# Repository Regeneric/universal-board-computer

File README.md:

# EXPERIMENTAL

Experimental branch for Pico W, written in Golang with TinyGO
Nothing works, really.

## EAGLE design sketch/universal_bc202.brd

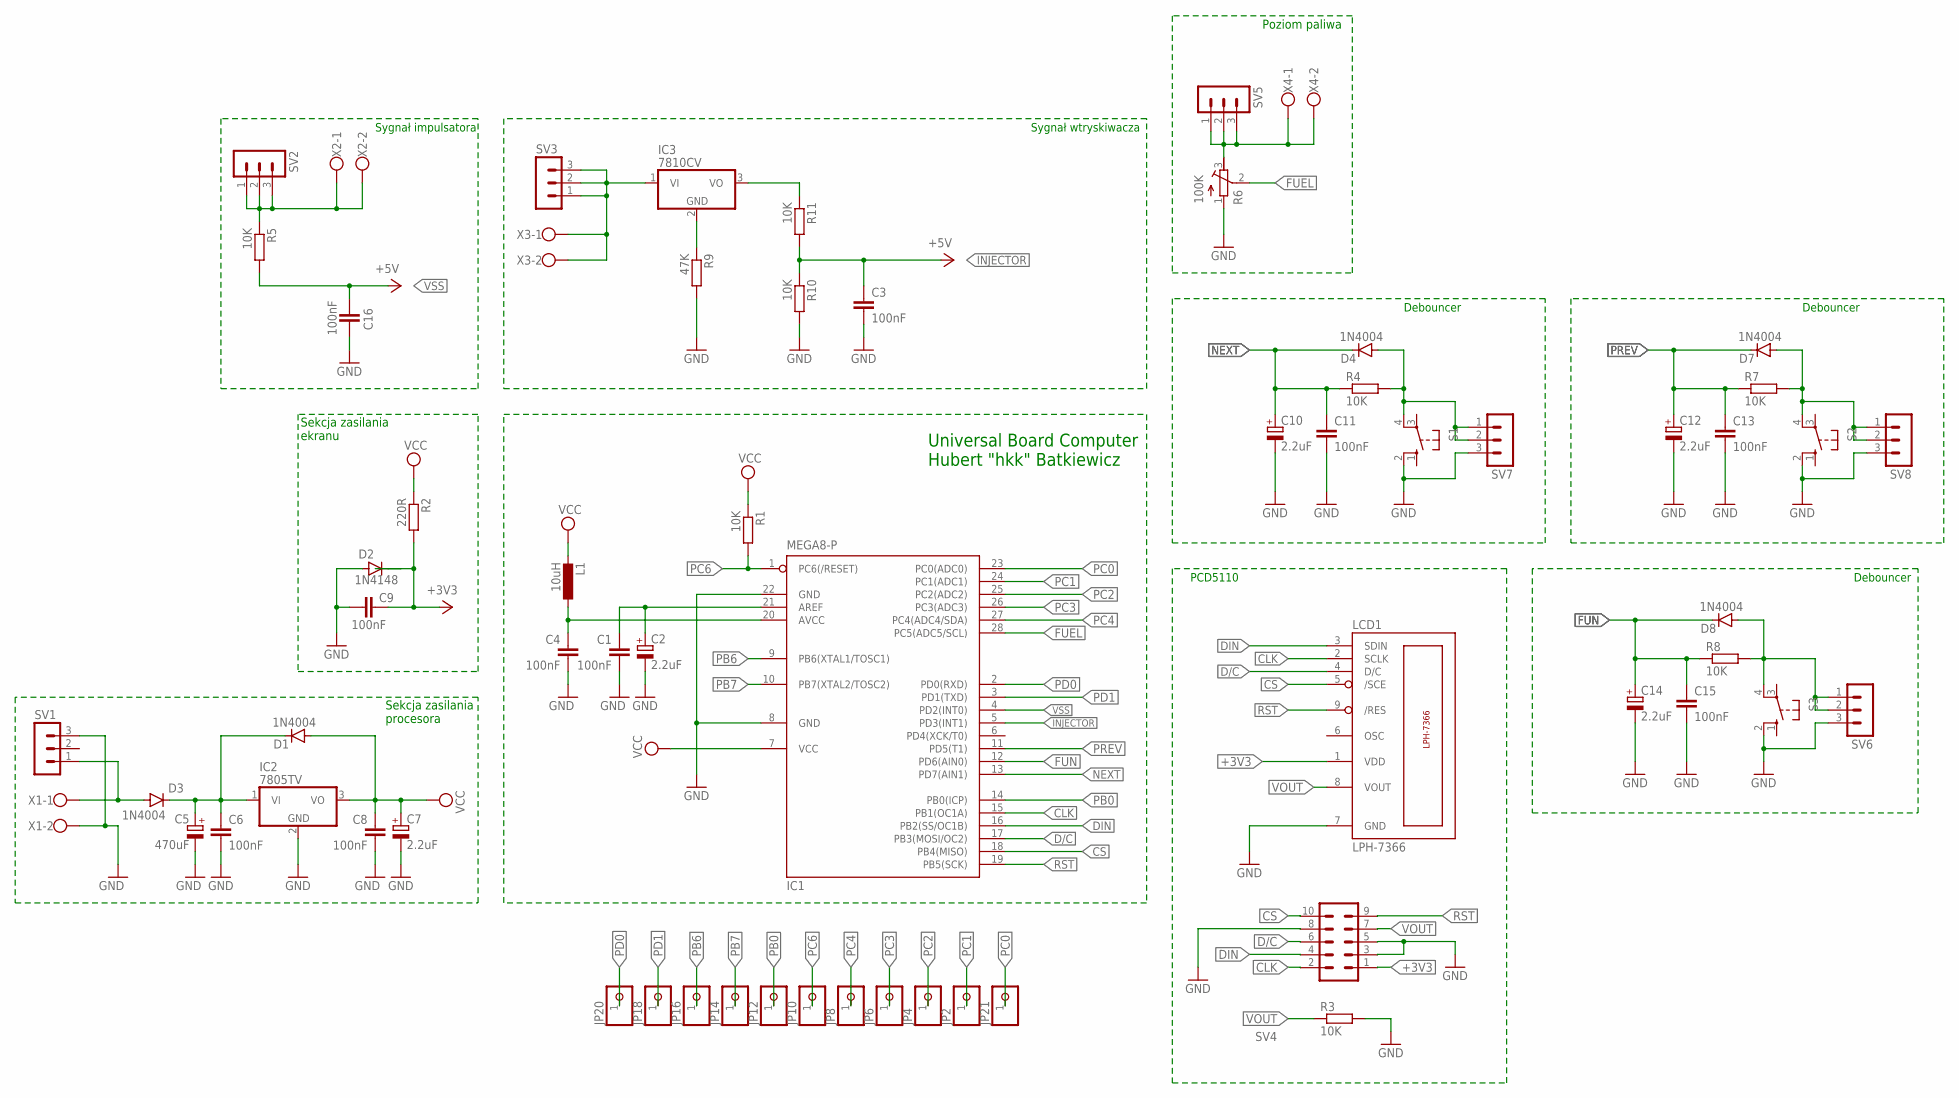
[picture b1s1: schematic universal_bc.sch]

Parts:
C1, C3, C4, C6, C8, C9, C11, C13, C15, C16: 100nF; C025-025X050
C2, C7, C10, C12, C14: 2.2uF; E2,5-6E
C5: 470uF; E2,5-6E
D1, D3, D4, D7, D8: 1N4004; DO41-10
D2: 1N4148; DO35-7
IC1: MEGA8-P; DIL28-3
IC2: 7805TV; TO220V
IC3: 7810CV; TO220V
JP2, JP4, JP6, JP8, JP10, JP12, JP14, JP16, JP18, JP20, JP21: PINHD-1X1; 1X01
L1: 10uH; 0207/2V
LCD1: LPH-7366
R1, R3, R4, R5, R7, R8, R10, R11: 10K; 0207/10
R2: 220R; 0207/10
R6: 100K; RTRIM3339P
R9: 47K; 0207/10
S1, S2, S3: 10-XX; B3F-10XX
SV1, SV2, SV3, SV5, SV6, SV7, SV8: MA03-1
SV4: MA05-2
X1, X2, X3, X4: W237-102

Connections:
+3V3: C9.1, D2.C, LCD1.1 (VDD), R2.2, SV4.1
CLK: IC1.15 (PB1(OC1A)), LCD1.2 (SCLK), SV4.2
CS: IC1.18 (PB4(MISO)), LCD1.5 (/SCE), SV4.10
D/C: IC1.17 (PB3(MOSI/OC2)), LCD1.4 (D/C), SV4.6
DIN: IC1.16 (PB2(SS/OC1B)), LCD1.3 (SDIN), SV4.4
FLOAT: R6.3 (E), SV5.1, SV5.2, SV5.3, X4.1, X4.2
FUEL: IC1.28 (PC5(ADC5/SCL)), R6.2 (S)
FUN: C14.+, C15.1, D8.C, IC1.12 (PD6(AIN0)), R8.1
GND: C1.2, C2.-, C3.2, C4.2, C5.-, C6.2, C7.-, C8.2, C9.2, C10.-, C11.2, C12.-, C13.2, C14.-, C15.2, C16.1, D2.A, IC1.8 (GND), IC1.22 (GND), IC2.2 (GND), LCD1.7 (GND), R3.2, R6.1 (A), R9.2, R10.2, S1.2 (S1), S2.2 (S1), S3.2 (S1), SV1.3, SV4.3, SV4.5, SV4.8, SV6.3, SV7.3, SV8.3, X1.2; also elsewhere on the board
INJECTOR: C3.1, IC1.5 (PD3(INT1)), R10.1, R11.2
unnamed: C1.1, C2.+, IC1.21 (AREF)
unnamed: C4.1, IC1.20 (AVCC), L1.1
unnamed: C5.+, C6.1, D1.C, D3.C, IC2.1 (VI)
unnamed: IC3.1 (VI), SV3.1, SV3.2, SV3.3, X3.1, X3.2
unnamed: D4.A, R4.2, S1.4 (P1), SV7.1, SV7.2
unnamed: D7.A, R7.2, S2.4 (P1), SV8.1, SV8.2
unnamed: D8.A, R8.2, S3.4 (P1), SV6.1, SV6.2
unnamed: D3.A, SV1.1, X1.1
unnamed: R5.1, SV2.1, SV2.2, SV2.3, X2.1, X2.2
unnamed: IC3.2 (GND), R9.1
unnamed: IC3.3 (VO), R11.1
NEXT: C10.+, C11.1, D4.C, IC1.13 (PD7(AIN1)), R4.1
PB0: IC1.14 (PB0(ICP)), JP12.1
PB6: IC1.9 (PB6(XTAL1/TOSC1)), JP16.1
PB7: IC1.10 (PB7(XTAL2/TOSC2)), JP14.1
PC0: IC1.23 (PC0(ADC0)), JP21.1
PC1: IC1.24 (PC1(ADC1)), JP2.1
PC2: IC1.25 (PC2(ADC2)), JP4.1
PC3: IC1.26 (PC3(ADC3)), JP6.1
PC4: IC1.27 (PC4(ADC4/SDA)), JP8.1
PC6: IC1.1 (PC6(/RESET)), JP10.1, R1.2; also elsewhere on the board
PD0: IC1.2 (PD0(RXD)), JP20.1
PD1: IC1.3 (PD1(TXD)), JP18.1
PREV: C12.+, C13.1, D7.C, IC1.11 (PD5(T1)), R7.1
RST: IC1.19 (PB5(SCK)), LCD1.9 (/RES), SV4.9
VCC: C7.+, C8.1, D1.A, IC1.7 (VCC), IC2.3 (VO), L1.2, R1.1, R2.1; also elsewhere on the board
VOUT: LCD1.8 (VOUT), R3.1, SV4.7
VSS: C16.2, IC1.4 (PD2(INT0)), R5.2

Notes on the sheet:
Sekcja zasilania procesora
Sekcja zasilania ekranu
Universal Board Computer Hubert "hkk" Batkiewicz
PCD5110
Sygnał impulsatora
Debouncer
Sygnał wtryskiwacza
Poziom paliwa

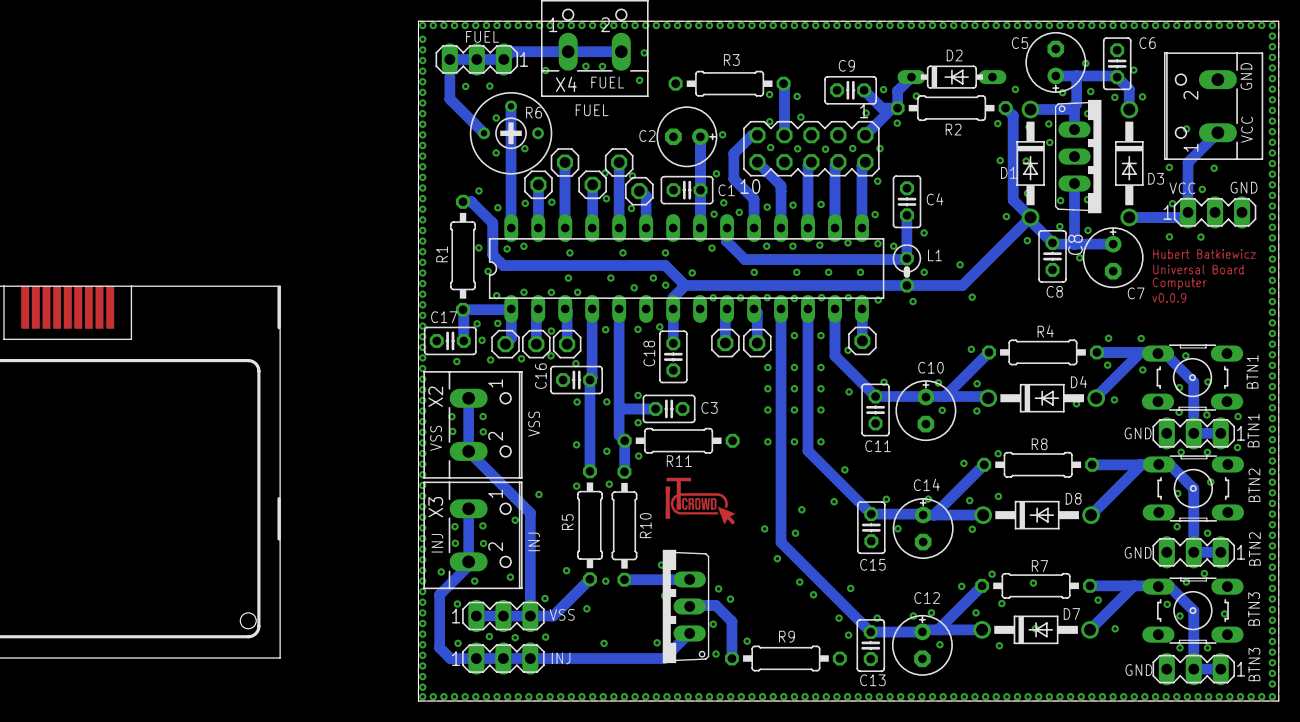
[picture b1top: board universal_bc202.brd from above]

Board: 2 copper layers, 81.0 x 64.0 mm, 66 parts (0 on the bottom side), 38 nets.

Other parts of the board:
C17: 10nF; C025-025X050
C18: 100nF; C025-025X050

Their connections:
GND: C17.2, C18.2; also elsewhere on the board
PC6: C17.1; also elsewhere on the board
VCC: C18.1; also elsewhere on the board

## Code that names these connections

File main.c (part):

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
    #define DHT_DDR  DDRD          
    #define DHT_PORT PORTD
    #define DHT_PIN  (1<<5)                    // PD5 as DHT11 pin

    #define DHT_EN_OUT  DHT_DDR |= DHT_PIN     // PD5 as output
    #define DHT_EN_INP  DHT_DDR &= ~DHT_PIN    // PD5 as input

    #define DHT_LO   DHT_PORT &= ~DHT_PIN      // Low state on PD5
    #define DHT_HI   DHT_PORT |= DHT_PIN       // High state on PD5

    typedef struct {
        float humidity;
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    } DHT; DHT dht;
#endif

#define USE_ADC              1        // 0 - don't use ADC for fuel readings;  1 - use ADC for fuel readings
#define INJECTORS            4        // Number of injectors

#define SAVE_INTERVAL        60       // Save data to EEPROM every X seconds
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
    #if USE_ADC == 1
    // ADC for checking fuel level
    DDRC &= ~(1<<PC5);                                // PC5/ADC as input

    ADCSRA |= ((1<<ADEN) | (1<<ADPS2) | (1<<ADPS1));  // Enables ADC and sets prescaller to 64 (8 MHz, 128 for 16 MHz)
    ADMUX |= ((1<<REFS1) | (1<<REFS0));               // Internal 1.1V ref voltage with external capacitor
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

    // VSS signal and injector signal - Atmega 328
    DDRD &= ~((1<<PD3) | (1<<PD2));      // PD3/INT1 and PD2/INT0 as input
    PORTD |= ((1<<PD3) | (1<<PD2));      // PD2/INT0 and PD3/INT1internal pull-up resistor to avoid high impedance state of the pin

    EICRA |= (1<<ISC01);                 // The FALLING edge on INT0 generates interrupt
    EICRA |= (1<<ISC10);                 // ANY change of state of INT1 generates interrupt
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    

    // Navigation buttons - Atmega 328
    DDRD &= ~((1<<PD7) | (1<<PD6));      // PD7/PCINT23 and PD6 as input    
    PORTD |= ((1<<PD7) | (1<<PD6));      // PD7/PCINT23 and PD6 internal pull-up resistor

    DDRB &= ~(1<<PB0);                   // PB0/PCINT0 as input
    PORTB |= (1<<PB0);                   // PB0/PCINT0 internal pull-up resistor

    PCICR |= ((1<<PCIE0) | (1<<PCIE2));  // Set PCIE0 and PCIE2 to enable PCMSK0 and PCMSK2 scan
    PCIFR |= ((1<<PCIF0) | (1<<PCIF2));  // Set PCIF0 and PCIF2 to enable interrupt flasg mask
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            fuelLeft = 40;
        #endif
        
        if(!(PIND & (1<<PD6)) && !buttonPressed) {
            while(i != 0) --i;
            i = 15;

            PORTD = i | (1<<PD6);
            buttonPressed = 1;

            if(calibrationFlag == 1 && mode == 2) {
                divideFuelFactor += 0.5f;
                eeprom_update_float(&eeSavedData.eeDivideFuelFactor, divideFuelFactor);
            }
        } else if((PIND & (1<<PD6)) && buttonPressed) {
            buttonPressed = 0;
            PORTD ^= (1<<PD6);
        } 
        
        if(!calibrationFlag) {
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    if(saveCounter <= 0 && injectorPulseTime < 800 && distPulseCount == 0) saveData();
    if(saveCounter <= 0 && speed == 0) saveData();

    if(!(PIND & (1<<PD6))) {
        --btnCnt;

        if(calibrationFlag == 0 && (btnCnt <= 20 && btnCnt > 0)) {
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
// Injector signal interrupt 
ISR(INT1_vect) {
    if(!(PIND & (1<<PD3))) injTimeLow = millis();  // Low state on PD3
    else {
        // High state on PD3
        injTimeHigh = millis();
        injectorPulseTime = injectorPulseTime + (injTimeHigh - injTimeLow);
        PORTD |= (1<<PD3);
    }
}


// Navigation buttons - Atmega 328
ISR(PCINT0_vect) {
    if(!(PINB & (1<<PB0))) {
        // Low state on PB0
        if(calibrationFlag == 1 &&  mode == 2 && !(PIND & (1<<PD6))) ccMin -= 0.5f;
        else if(calibrationFlag == 1 && mode == 3 && !(PIND & (1<<PD6))) distPulseCount -= 500;
        else if(calibrationFlag == 0 && mode == 1 && !(PIND & (1<<PD6))) {
            fuelLeft -= 0.5f;
            savedFuel = fuelLeft;
            eeprom_update_float(&eeSavedData.eeSavedFuel, savedFuel);
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}

ISR(PCINT2_vect) {
    if(!(PIND & (1<<PD7))) {
        // Low state on PD7
        if(calibrationFlag == 1 && mode == 2 && !(PIND & (1<<PD6))) ccMin += 0.5f;
        else if(calibrationFlag == 1 && mode == 3 && !(PIND & (1<<PD6))) distPulseCount += 500;
        else if(calibrationFlag == 0 && mode == 1 && !(PIND & (1<<PD6))) {
            fuelLeft += 0.5f;
            savedFuel = fuelLeft;
            eeprom_update_float(&eeSavedData.eeSavedFuel, savedFuel);
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
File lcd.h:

//  ​Universal Board Computer for cars with electronic MPI
//  Copyright © 2015, 2021-2022 IT Crowd, Hubert "hkk" Batkiewicz; 
//  Sergey Denisov aka LittleBuster (DenisovS21@gmail.com)
// 
//  This file is part of UBC.
//  UBC is free software: you can redistribute it and/or modify
//  ​it under the terms of the GNU Affero General Public License as
//  published by the Free Software Foundation, either version 3 of the
//  ​License, or (at your option) any later version.
// 
//  ​This program is distributed in the hope that it will be useful,
//  ​but WITHOUT ANY WARRANTY; without even the implied warranty of
//  ​MERCHANTABILITY or FITNESS FOR A PARTICULAR PURPOSE. 
//  See the ​GNU Affero General Public License for more details.
// 
//  ​You should have received a copy of the GNU Affero General Public License
//  ​along with this program.  If not, see <https://www.gnu.org/licenses/>

// <https://itcrowd.net.pl/>
// <https://github.com/LittleBuster>


#ifndef LCD_H
#define LCD_H

#include <avr/pgmspace.h>
#include <stdint.h>

// LCD's port
#define PORT_LCD PORTB
#define DDR_LCD  DDRB

// LCD's pins
#define LCD_RST PB5  // RST
#define LCD_SCE PB4  // CS
#define LCD_DC  PB3  // D/C
#define LCD_DIN PB2  // DIN
#define LCD_CLK PB1  // CLK

#define LCD_CONTRAST 0x40

struct lcdInterface {
    void (*init)(void);
    void (*clear)(void)  __attribute__((optimize("-O3")));
    void (*sendc)(char code, uint8_t scale);
    void (*sends)(const char* word, uint8_t scale);
    void (*cursor)(uint8_t xPos, uint8_t yPos);
    void (*render)(void) __attribute__((optimize("-O3")));
    // void (*power)(uint8_t on);
    // void (*setPixel)(uint8_t xPos, uint8_t yPos, uint8_t value);
}; extern const struct lcdInterface LCD;

#endif  // LCD_H

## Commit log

2021-01-27 Harmonic mean for avg speed and fuel cons
2021-01-27 EEPROM data type corrected for avgSpeedDivider
2021-02-01 AGPL license, some tweaks with memory
2021-02-07 Memory optimalization (224... bytes of free space in flash).
2021-02-07 Memory optimalization and speed calibration menu
2021-02-07 Fuel 'gauge' feature
2021-02-16 Reset values from the EEPROM and display
2021-02-25 atmega 328 basic functionality
2021-02-28 Data reset in EEPROM - problem
2021-03-04 EEPROM problem
2021-03-08 Sailing time and acceleration measure on road
2021-03-08 Sailing time, acceleration measure on road and readme
2022-11-24 Pico W and Golang
2022-11-27 UBC RTOS - EXPERIMENTAL
2022-12-16 UBC - new functions and bugfixes

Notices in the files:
main.c:
Copyright © 2021-2022 IT Crowd, Hubert "hkk" Batkiewicz
